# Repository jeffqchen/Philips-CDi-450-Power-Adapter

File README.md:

# Philips CD-i 450/550 Power Adapter

------
## Update: Alternative Solution You Can Buy - G2 PSU

Zaxour designed a new replacement power supply that takes a single power input and converts it to all the necessary power rails. I had the honor to design a shell for it.

You can actually purchase the G2 PSU [here](https://ko-fi.com/s/8996431f0d).

------
## Rambling

The Philips CD-i 450/550 has a weird PSU (Type 20 PS 301/XX, 20PS301, 22ER9156). It uses an RJ45 jack to connect to the console.

Everybody familiar with ethernet cables knows the plastic tab on an RJ45 plug will snap off sooner or later. Then the plug will become loose and start falling out of the jack. While it might not be that devastating on a network connection, it is unacceptable for a power connection. Not to mention that over the decades, some consoles were separated from their original PSU, and replacements are expensive while supplies being limited.

------
## Functionality

### Power Sources

This adapter utilizes TWO **Center-Positive 5V** power adapters, with the plug dimension of **5.50mm OD (0.217") and 2.10mm ID (0.083")**.

**Do NOT** use a Y-adapter with a single power source or your adapter will short and die.

The one on the left requires 3.3A (16.5W). I call this the "beefy" one.

The one on the right is a weak one that any 5V adapter you can find will be more than capable to handle the job.

These power rating specs are the lowest requirements. You can go higher but not lower.

### Transmission Cable

Use a **straight** RJ45 ethernet cable in short length. The wiring order on the two ends of the cable should be **exactly the same** or bad things will happen. It's easy to test with a meter if visual inspection is difficult.

### Usage

Plug everything in and use the power switch on the CD-i itself to turn the power on/off.

------
## Parts
- PCB - [Link](https://oshpark.com/shared_projects/HBbJdevy)
- [2x] PJ-002A Barrel Jack, OD 5.50mm / ID 2.10mm - [Link](https://github.com/jeffqchen/JeffParts/blob/main/Connectors/Barrel%20Jack/PJ-002A/info.md)
- 1705951 RJ45 Ethernet Jack, Female - [Link](https://github.com/jeffqchen/JeffParts/blob/main/Connectors/RJ45/Female/1705951/info.md)
- J104A2C5VDC.40S General Purpose Relay, DPDT, 5V/3A - [Link](https://github.com/jeffqchen/JeffParts/blob/main/Components/J104A2C5VDC.40S%20Relay/info.md)
- M3x20mm hex screw and nut - [Link](https://github.com/jeffqchen/JeffParts/blob/main/Parts/M2%20M3%20Hex%20Screw%20%26%20Nut/info.md)
- 3D Printed Case - [Link](https://github.com/jeffqchen/Philips-CDi-450-Power-Adapter/tree/main/3D%20Print)

**Optional Parts**
- 1N4148W Diode, SMD - [Link](https://github.com/jeffqchen/JeffParts/blob/main/Components/1N4148W/info.md) (for possible extending lifespan of relay coil)
- LEDs for power state indication
  - Two of each color, with their respective current limiting resistor (0805 size or smaller)
  - Typical LED forward voltage range from 2V to 3.2V. 100-150 Ohm resistors is a good choice.

### Power Sources

- "Beefy" WSU050-4000, 5V/20W, OD5.5mm/ID2.1mm, Triad Power Adapter - [Link](https://github.com/jeffqchen/JeffParts/blob/main/Power/WSU050-4000/info.md)
- WSU050-1500, 5V/7.5W OD5.5mm/ID2.1mm, Triad Power Adapter - [Link](https://github.com/jeffqchen/JeffParts/blob/main/Power/WSU050-1500/info.md) (but really, any 5V adapter will do)

------
## 3D Printing The Shell

Print the parts as shown in the following pics, with support.

------
## Assembly

### Populating Components

Populate the PCB with parts. Trim the extra length of extruding legs but no need to go crazy.

#### LEDs

D1 and D2 are for standby and D3 and D4 are for running. Choose your colors accordingly.

If in case one side does not light up, please check your power sources first as there might be a serious problem.

### Closing The Case

Fit into the bottom shell. Close the top shell over.

Drop the nut inside the cavity, then tighten the screwn from the bottom.

Drop in the top lid inside, fit one side in position first, then press and snap the other side into the slot.

This concludes the assembly.

------
## Special Thanks

- Retrostuff (for suggesting various technical details about the Philips CD-i)
  - [Twitter](https://twitter.com/retrostuff_org)
  - [Website](https://retrostuff.org/)

------
Shield: [![CC BY-SA 4.0][cc-by-sa-shield]][cc-by-sa]

This work is licensed under a
[Creative Commons Attribution-ShareAlike 4.0 International License][cc-by-sa].

[![CC BY-SA 4.0][cc-by-sa-image]][cc-by-sa]

[cc-by-sa]: http://creativecommons.org/licenses/by-sa/4.0/
[cc-by-sa-image]: https://licensebuttons.net/l/by-sa/4.0/88x31.png
[cc-by-sa-shield]: https://img.shields.io/badge/License-CC%20BY--SA%204.0-lightgrey.svg

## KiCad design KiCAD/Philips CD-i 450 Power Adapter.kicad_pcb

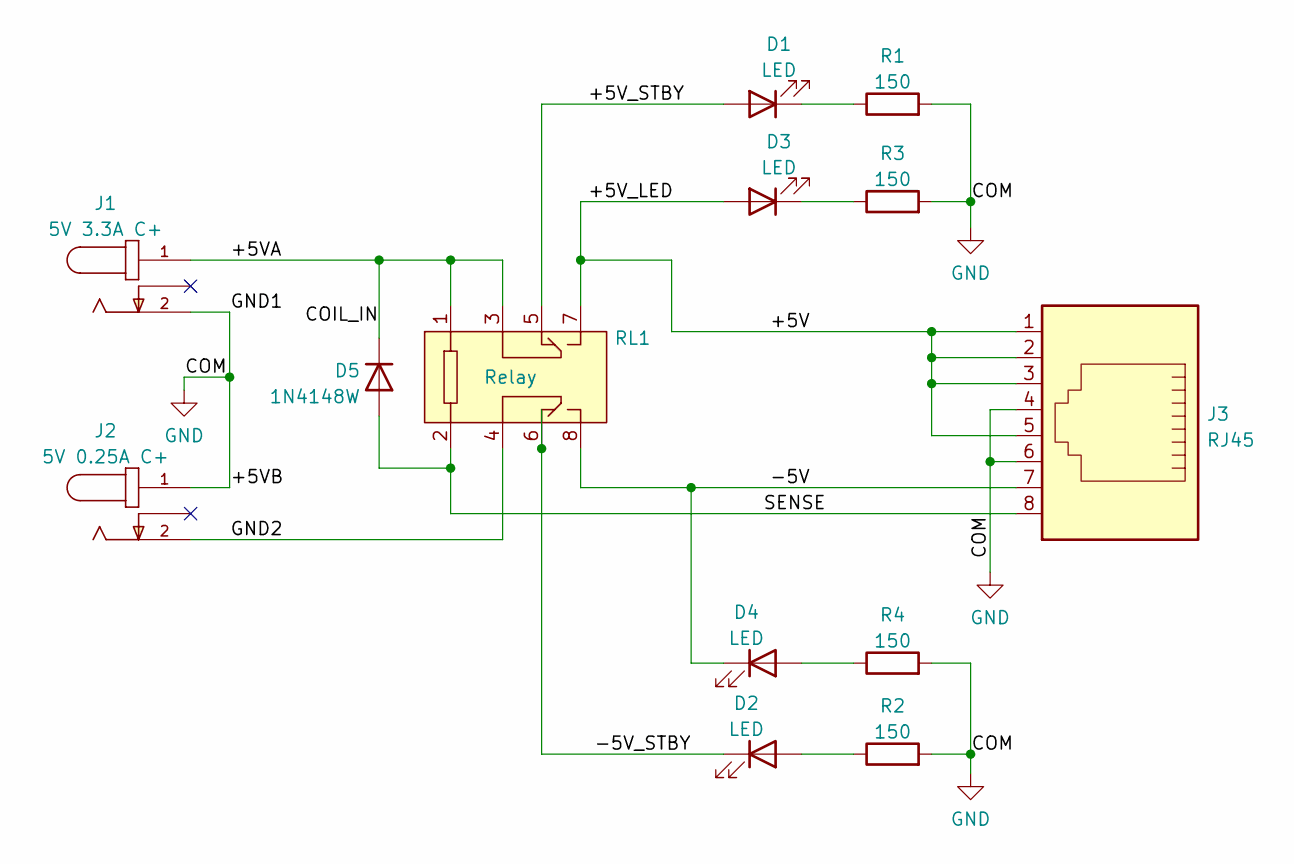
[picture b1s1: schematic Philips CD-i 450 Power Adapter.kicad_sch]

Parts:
D1, D2, D3, D4: LED; LED_D5.0mm
D5: 1N4148W; D_SOD-123
J1: 5V 3.3A C+; CUI_PJ-002A
J2: 5V 0.25A C+; CUI_PJ-002A
J3: RJ45
R1, R2, R3, R4: 150; R_0805_2012Metric_Pad1.20x1.40mm_HandSolder
RL1: Relay

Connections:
/+5V: D3.2 (A), J3.1, J3.2, J3.3, J3.5, RL1.7
/+5VA: D5.1 (K), J1.1, RL1.1, RL1.3
/+5V_STBY: D1.2 (A), RL1.5
/-5V: D4.1 (K), J3.7, RL1.8
/-5V_STBY: D2.1 (K), RL1.6
/GND2: J2.2, RL1.4
/SENSE: D5.2 (A), J3.8, RL1.2
GND: J1.2, J2.1, J3.4, J3.6, R1.2, R2.2, R3.2, R4.2
unnamed: D1.1 (K), R1.1
unnamed: D2.2 (A), R2.1
unnamed: D3.1 (K), R3.1
unnamed: D4.2 (A), R4.1

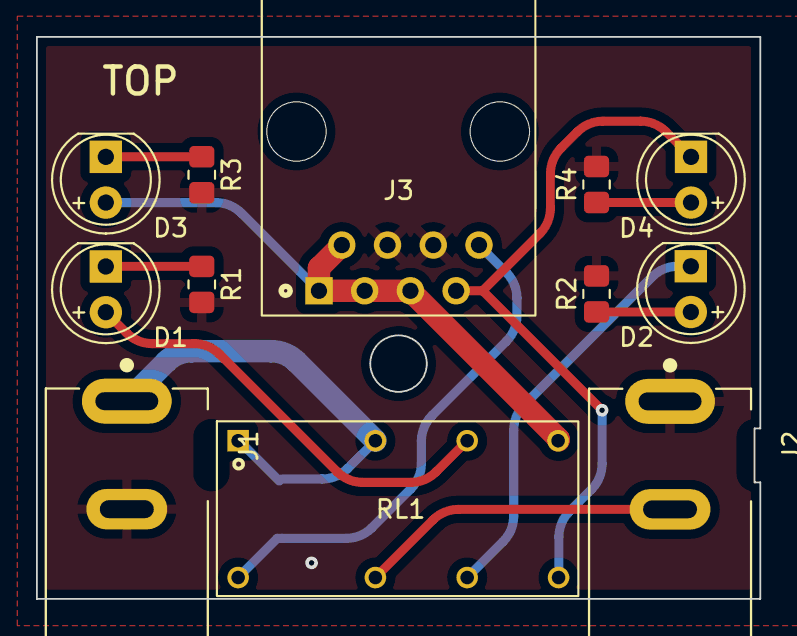
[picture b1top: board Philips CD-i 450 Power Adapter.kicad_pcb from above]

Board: 2 copper layers, 40.2 x 31.2 mm, 13 parts (1 on the bottom side), 12 nets.

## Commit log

2022-11-29 Initial Upload
2022-11-29 Add license
2022-11-29 Add photo
2025-02-26 Update README.md
    Add G2 PSU link
